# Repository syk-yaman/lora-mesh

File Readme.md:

# LoRaMesh: a LoRa mesh network deployed in the Olympic Park, London to sense weather parameters

##### A dissertation for an MSc degree in [Connected Environments](https://connected-environments.org/) at [University College London](https://www.ucl.ac.uk/prospective-students/graduate/taught-degrees/connected-environments-msc), 2022/2023.

This project uses [OpenThread](https://openthread.io/) in LoRa to sense humidity, temperate and light in the Queen Elizabeth Olympic Park (QEOP), London. Sensor data is visualised via web dashboards and projected on a physical Olympic Park table using projection mechanism.

|                          Mesh node                           |                The Data Table                 |
| :----------------------------------------------------------: | :-------------------------------------------: |
|  |  |

## Repository Content Summary

1. **Assets**

   This folder includes the 3D printed parts, namely Fusion360 project files and STLs for the enclosures and the 3D objects for the Data Table.

   - [QEOP 3D Models](</Assets/QEOP 3D models/>)
   - [LoRa Gateway 3D Enclosures](</Assets/3D Enclosures/>)

2. **Code**

   Includes micro-controllers' code, Artificial Intelligence code and various assets used during development.

   - [Lopy4](/Code/Lopy4)

     The main Micro Python code for the Lopy4, which uses Open Thread for LoRa mesh.

   - [Current Analysis](/Code/Current%20Analysis)

     Contains the code, schematic and results for the real-time current analysis circuit.

   - [Heatmap](/Code/Heatmap)

     Web page that visualises CSV data for LoRa heatmap in the Olympic Park.

   - [VR Headset](/Code/VR%20Headset)

     A web page built using [A-Frame](https://aframe.io/) to visualise 360 videos of the QEOP on VR Headsets.

   - [Data Table](</Code/DataTable>)
     The data files projected on the physical map including the final calibrated [Base Map](/Code/DataTable/BaseMap.jpg).

3. **Datasets**

   The final datasets as an outcome of this project. There is a [detailed description](/Datasets/Readme.md) available for each dataset.
   
4. **Docs**

   This folder holds different kinds of documentation and images produced during project life time.

5. **PCB**

   The electronic side of the project. This section contains Eagle files and CAM outputs sent to PCB manufacturers. Also, a [CNC manufacturing tutorial](/PCB/CNC) is available.

6. **Server**

   Docker Composer file for InfluxDB, Grafana and MQTT broker. Basically, all data acquisition is being managed by this Docker image.

7. **Experiments**
   This section includes the multiple experiments done throughout the project.

   - [Experiment #1](/Experiments/Experiment1): First heatmap between LoRa indoor gateway and MRK1310.
   - [Experiment #2](/Experiments/Experiment2): Heatmap between two LoRa nodes (Both MRK1310).
   - [Experiment #3](/Experiments/Experiment3): Heatmap between two LoRa nodes (Both Lopy4), contains a [geolocated dataset](/Experiments/Experiment3/Results/heatmap/Experiment3-LoRa-RSSI-heatmap-QEOP-OPS.csv).
   - [Experiment #4](/Experiments/Experiment4): Contains a [topographic study](/Experiments/Experiment4/GIS%20Stratford) using QGIS, and a [detailed deployment plan](/Experiments/Experiment4/Deployment%20plan) for LoRa nodes in the QEOP.
   - [Experiment #5](/Experiments/Experiment5): Basic Pymesh experiments. 
   - [Experiment #6](/Experiments/Experiment6): Basic MQTT experiments.

## Project Overview

## Building

### Used components and tools

Hardware:

* [Lopy4](https://www.adafruit.com/product/3689): a dev kit based on ESP32 that has LoRa, Wifi, Sigfox and Bluetooth communication capability.
* [SHT-30](https://www.adafruit.com/product/4099): a weatherproof humidity and temperature sensor.
* [Gravity SEN0562](https://www.dfrobot.com/product-2664.html): a weatherproof light sensor.
* [DC Solar charger (BQ24074)](https://www.adafruit.com/product/4755)
* [Solar panel](https://coolcomponents.co.uk/products/solar-panel-1-watt): 1 Watt, 10x80 cm.
* 2000 mA 3.7v battery

Software:

 - [InfluxDB](https://www.influxdata.com/)
 - [Telegraf](https://www.influxdata.com/time-series-platform/telegraf/)
 - [Grafana](https://grafana.com/)
 - [Docker Compose](https://docs.docker.com/compose/)

All the software applications are packed into one [Docker image](/Server/docker-compose.yml) that you can use easily.

### Hardware PCB and schematic

## Results

#### The Data Table

#### Grafana Dashboard

#### Heatmaps

#### Current consumption analysis

## License

###### The software side is licensed under MIT License

```
MIT License

Permission is hereby granted, free of charge, to any person obtaining a copy
of this software and associated documentation files (the "Software"), to deal
in the Software without restriction, including without limitation the rights
to use, copy, modify, merge, publish, distribute, sublicense, and/or sell
copies of the Software, and to permit persons to whom the Software is
furnished to do so, subject to the following conditions:

The above copyright notice and this permission notice shall be included in all
copies or substantial portions of the Software.

THE SOFTWARE IS PROVIDED "AS IS", WITHOUT WARRANTY OF ANY KIND, EXPRESS OR
IMPLIED, INCLUDING BUT NOT LIMITED TO THE WARRANTIES OF MERCHANTABILITY,
FITNESS FOR A PARTICULAR PURPOSE AND NONINFRINGEMENT. IN NO EVENT SHALL THE
AUTHORS OR COPYRIGHT HOLDERS BE LIABLE FOR ANY CLAIM, DAMAGES OR OTHER
LIABILITY, WHETHER IN AN ACTION OF CONTRACT, TORT OR OTHERWISE, ARISING FROM,
OUT OF OR IN CONNECTION WITH THE SOFTWARE OR THE USE OR OTHER DEALINGS IN THE
SOFTWARE.
```

###### The hardware side is licensed under CERN License

```
This documentation describes Open Hardware and is licensed under the CERN OHL v. 1.2.

You may redistribute and modify this documentation under the terms of the CERN OHL v.1.2. (http://ohwr.org/cernohl). This documentation is distributed WITHOUT ANY EXPRESS OR IMPLIED WARRANTY, INCLUDING OF MERCHANTABILITY, SATISFACTORY QUALITY AND FITNESS FOR A PARTICULAR PURPOSE. Please see the CERN OHL v.1.2 for applicable conditions
```

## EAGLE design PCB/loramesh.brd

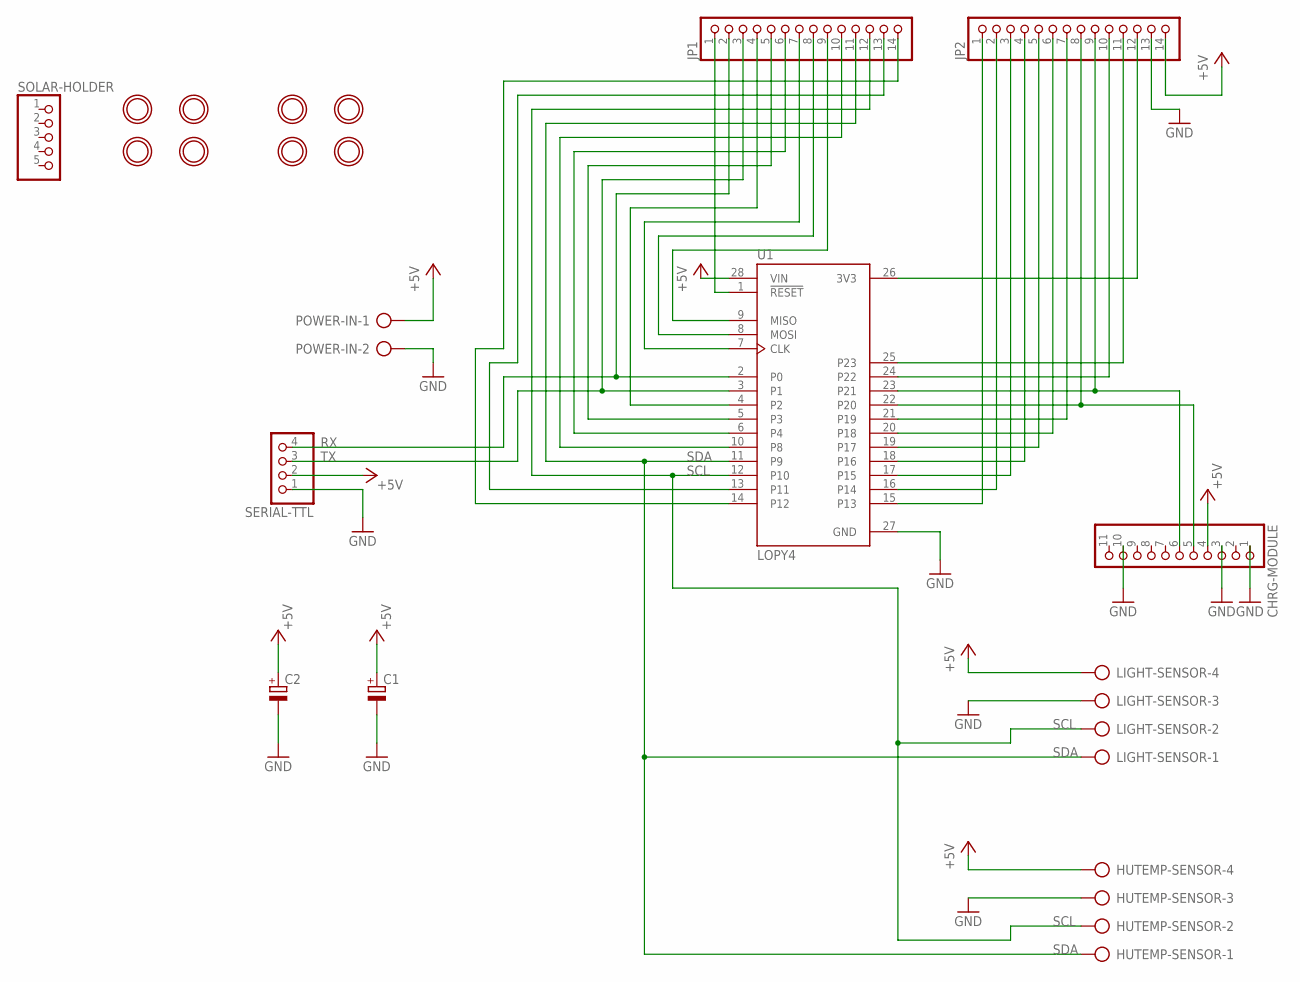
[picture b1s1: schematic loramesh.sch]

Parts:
C1, C2: CPOL-EUE2.5-5; E2,5-5
CHRG-MODULE: HEADER-1X1176MIL; 1X11_ROUND_76
HUTEMP-SENSOR: AK500/4
JP1, JP2: PINHD-1X14; 1X14
LIGHT-SENSOR: AK500/4
POWER-IN: AK500/2
SERIAL-TTL: PINHD-1X4; 1X04
SOLAR-HOLDER: PINHD-1X5; 1X05
U1: LOPY4; MODULE_LOPY4
U$1, U$2, U$3, U$4, U$26, U$27, U$28, U$29: MOUNTINGHOLE2.5; MOUNTINGHOLE_2.5_PLATED

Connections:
+5V: C1.+, C2.+, CHRG-MODULE.4, HUTEMP-SENSOR.4, JP2.14, LIGHT-SENSOR.4, POWER-IN.1, SERIAL-TTL.2, U1.28 (VIN)
GND: C1.-, C2.-, CHRG-MODULE.1, CHRG-MODULE.3, CHRG-MODULE.10, HUTEMP-SENSOR.3, JP2.13, LIGHT-SENSOR.3, POWER-IN.2, SERIAL-TTL.1, U1.27 (GND)
unnamed: CHRG-MODULE.5, JP2.8, U1.22 (P20)
unnamed: CHRG-MODULE.6, JP2.9, U1.23 (P21)
unnamed: JP1.1, U1.1 (!RESET)
unnamed: JP1.14, U1.14 (P12)
unnamed: JP1.13, U1.13 (P11)
unnamed: JP1.4, U1.4 (P2)
unnamed: JP1.5, U1.5 (P3)
unnamed: JP1.6, U1.6 (P4)
unnamed: JP1.7, U1.7 (CLK)
unnamed: JP1.8, U1.8 (MOSI)
unnamed: JP1.9, U1.9 (MISO)
unnamed: JP1.10, U1.10 (P8)
unnamed: JP2.1, U1.15 (P13)
unnamed: JP2.2, U1.16 (P14)
unnamed: JP2.3, U1.17 (P15)
unnamed: JP2.4, U1.18 (P16)
unnamed: JP2.5, U1.19 (P17)
unnamed: JP2.6, U1.20 (P18)
unnamed: JP2.7, U1.21 (P19)
unnamed: JP2.10, U1.24 (P22)
unnamed: JP2.11, U1.25 (P23)
unnamed: JP2.12, U1.26 (3V3)
RX: JP1.2, SERIAL-TTL.4, U1.2 (P0)
SCL: HUTEMP-SENSOR.2, JP1.12, LIGHT-SENSOR.2, U1.12 (P10)
SDA: HUTEMP-SENSOR.1, JP1.11, LIGHT-SENSOR.1, U1.11 (P9)
TX: JP1.3, SERIAL-TTL.3, U1.3 (P1)

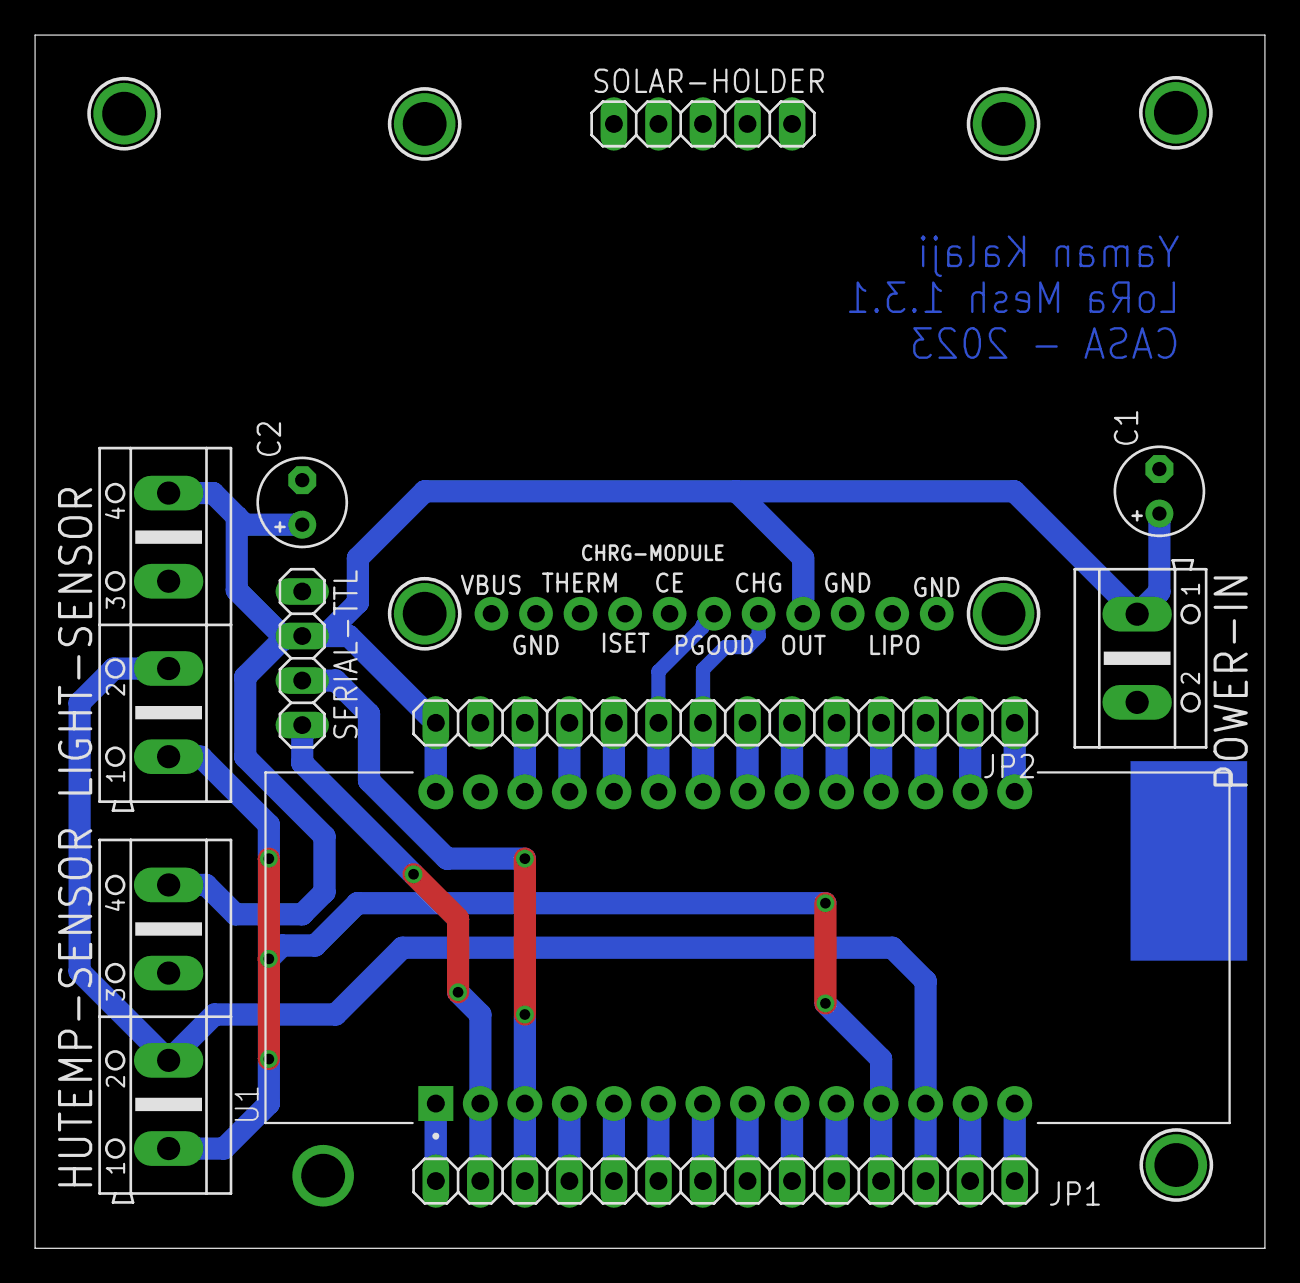
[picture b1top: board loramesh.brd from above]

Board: 2 copper layers, 70.2 x 69.2 mm, 19 parts (1 on the bottom side), 28 nets.

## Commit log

2023-03-27 Add Mikrotik LoRa gateway 3D case
2023-03-27 Change router case name to be v1
2023-03-27 Add v2 of Router Holder
2023-03-27 Add v3 of Gateway case
2023-03-27 V4 of gateway case
2023-03-27 V5 of gateway case
2023-03-27 Add Fusion 360 file of Gateway case v6
2023-03-27 Add the code for LoRa heatmap experiment in One Pool Street, London
2023-04-13 Add the results of the LoRa heatmap experiment #2
2023-05-02 Add the code for first connection between two Lopy4s
2023-05-02 Restructure files and folders
2023-05-02 Remove redundant files
2023-05-02 Add the sender code for experiment 3
2023-05-02 Complete files and folders restructuring
2023-05-02 Add some photos for experiment 3
2023-05-02 Added an interactive heatmap with the 3rd experiment results
2023-05-31 Add a SH31 temperature and humidity test script & results
2023-05-31 Try to make the light sensor work, the code doesn't work because it contains a special character
2023-05-31 Try to fix the code by replacing the special character with its binary equivalent - not working
2023-05-31 Added the datasheet for the main IC of the light sensor
2023-05-31 Found the right I2C code, now the code is working
2023-05-31 Add sensor light results
2023-07-10 Add some raw results for the light sensor (SEN0562)
2023-07-10 Disable the heater to get accurate results
2023-07-10 Add mesh network deployment plan in the QEOP
2023-07-10 Move files in experiment 4
2023-07-10 Add OPS deployment plan photos
2023-07-10 Add QEOP deployment plan photos
2023-07-10 Add QEOP topographic analysis photos
2023-07-10 Add QEOP deployment plan with the topographic photos
2023-07-10 Add the QGIS project file
2023-07-10 Ignore downloaded maps in the QGIS project folder
2023-07-10 Try to merge all sensors
2023-08-02 Add experiment 5 code: Pymesh activation and provisioning
2023-08-02 Fix a bug in the Pycom's code, maybe the example I'm using is old
2023-08-05 Remove humidity sensor and start from the beginning again
2023-08-05 Temperature sensor is working now via I2C
2023-08-05 Ignore the data table code because it falls under Steve's authority
2023-08-05 Refactor the all sensors code
2023-08-05 Also code cleaning
2023-08-07 Add PCB files (sent to China)
2023-08-09 Restructure 3D printed files
2023-08-09 Add a VR headset code for 360 video in the park
2023-08-09 Ignored the Google Earth Studio video files, due to their license
2023-08-09 Add exported photos of the PCB
2023-08-09 Add the generated CAM outputs for later CNC job
2023-08-09 Add FlatCAM PCB project file for the CNC machine
2023-08-09 Add the generated Gcodes for CNC machine
2023-08-11 Fixed the problem in CNC Carvey (Inventables) by replacing the CNC GCode with an older version generated by FlatCam v8.5
2023-08-11 Add the new FlatCam project
2023-08-11 Added settings used to mill the first PCB using Carvey CNC machine, also reached a conclusion after breaking 3 pits that I need a V shaped pit for etching
2023-08-15 Add steps documentation for manufacturing a PCB using a CNC
2023-08-17 Adding MQTT library to the code
2023-08-17 Add the printed version of the Aquatic Centre
2023-08-17 Add the print optimised version of the Aquatic Centre
2023-08-17 Add models credits
2023-08-17 Fix some images
2023-08-17 Also fix images
2023-08-17 Stop tracking redundant files
2023-08-17 Add data table code folder - for later
2023-08-17 Add heatmap webpage code
2023-08-17 Trying to get links work
2023-08-17 Add the Lopy4 code after long experiments
2023-08-17 Rename secrets file to config due to a conflict in Python libraries
2023-08-17 Add a config example for future usage
2023-08-17 Add a comment to the config file
2023-08-19 My SHT30 Python implementation didn't fully work, found a library for that
2023-08-19 Modify the SHT30 library to be compatible with my sensor and Lopy4
2023-08-19 Add credits
2023-08-19 Edit project name
2023-08-19 Connect sensors to MQTT and my InfluxDB
2023-08-21 Add London Stadium to the QEOP 3D models
2023-08-21 Add the Arcelor Mittal Orbit 3D model
2023-08-25 Change folder name
2023-08-25 Add current analysis code
2023-08-25 Add current consumption results
2023-08-25 Add server code
2023-08-25 Add the code for current analysis using INA169
2023-08-25 Push some old code
2023-08-25 Add system overviews
2023-08-25 Add the schematic for current analysis circuit
2023-08-25 Add project proposal and system overview diagram Draw.io file
2023-08-25 Add the graphs file (using Magic Plot software)
2023-08-25 Add some docs
2023-08-25 Update docs
2023-08-25 Add PCB images
2023-08-25 Try centering an image
2023-08-25 Resizing images
2023-08-25 Correct system overview diagram
2023-08-25 Add an inside image of the deployed box
2023-08-25 Remove JS files in the VR headset folder and replace them with CDN version
2023-08-25 Compress the CNC G-Code files
2023-08-26 Some images edited
2023-08-26 Add the calibrated Base Map of the Data Table
2023-08-26 Add humidity map for the Data Table
2023-08-26 Add the indoor LoRa map for the Data Table
2023-08-26 Add the outdoor LoRa map for the Data Table
2023-08-26 Add the topographic map for the Data Table
2023-08-26 More pics
2023-08-26 Fixes
2023-08-26 Remove redundant datasheet from docs
2023-08-28 Organise the datasets into one folder
2023-08-28 Add the datasets exporter from InfluxDB
2023-08-28 Add a datasets readme file
2023-08-28 Images correction and updates
2023-08-28 Add datasets to the main readme.md
2023-08-28 Correct a typo
2023-09-04 Finished designing a 3D model for Marshgate from scratch
2023-09-04 Update QEOP 3d models description
